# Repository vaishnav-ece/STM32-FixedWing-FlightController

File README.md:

# STM32-FixedWing-FlightController
Custom STM32-based flight controller PCB for fixed-wing UAVs featuring IMU and barometer integration, PWM servo outputs, UART/SPI/I2C/CAN interfaces, USB-C debugging, low-noise power design, PID stabilization architecture, and custom KiCad footprint development.

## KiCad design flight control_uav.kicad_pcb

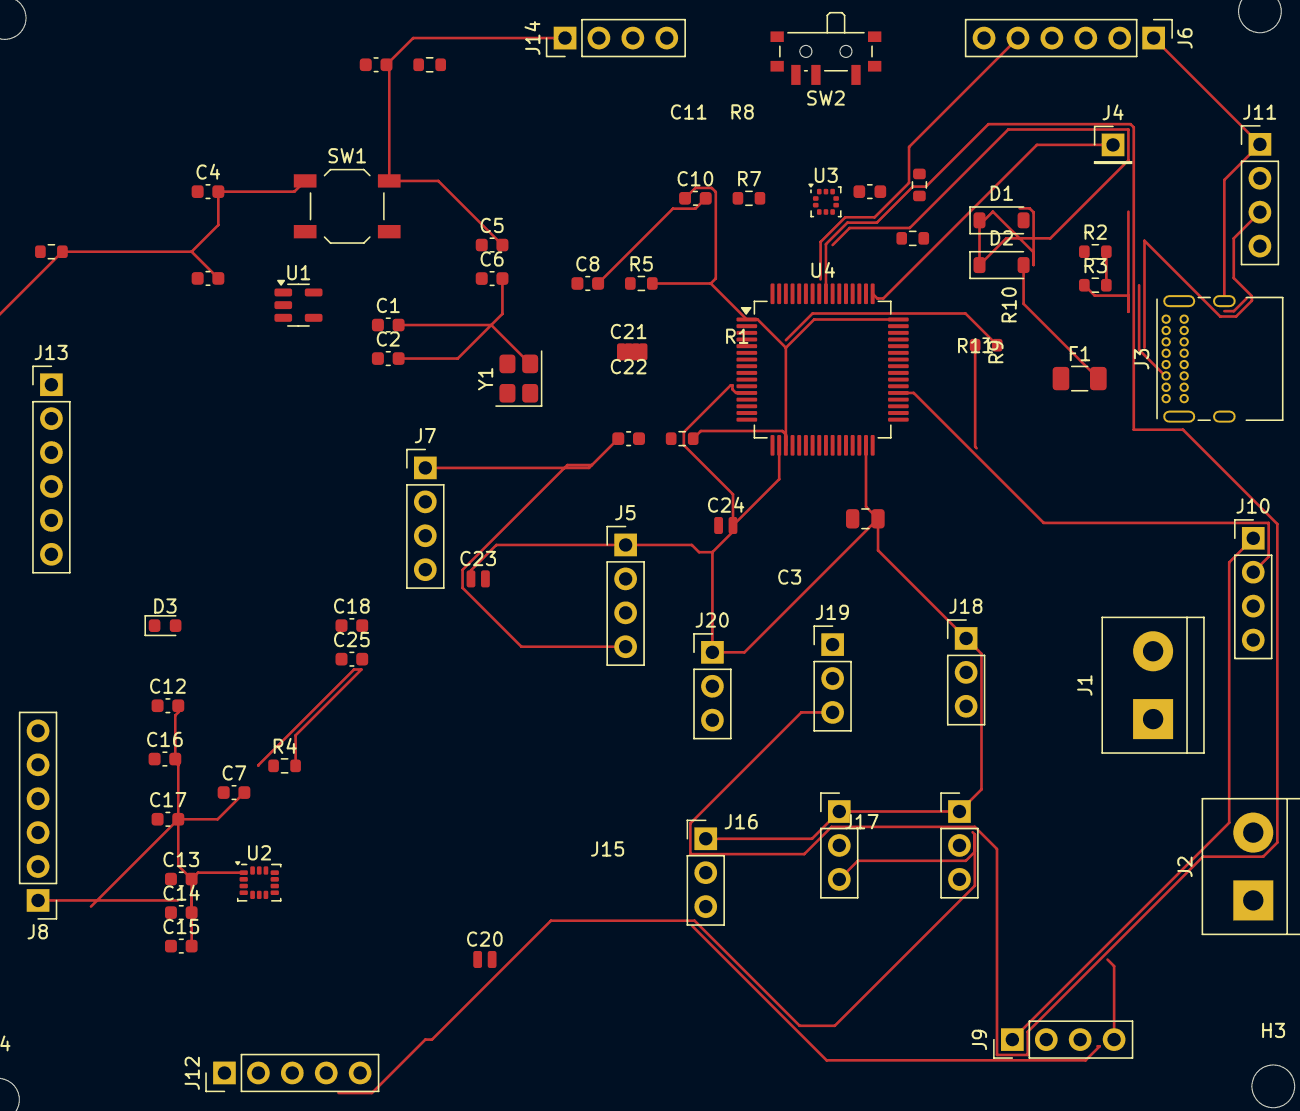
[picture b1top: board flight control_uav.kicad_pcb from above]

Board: 2 copper layers, 72 parts (0 on the bottom side), 59 nets.

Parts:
C1, C5, C6, C8, C13, C14, C15, C16, C17, C18, C25: 100n; C_0603_1608Metric
C2, C4, C7: 2u2; C_0603_1608Metric
C3, C9: 10n; C_0603_1608Metric
C10, C11: C; C_0603_1608Metric
C12: 10u; C_0603_1608Metric
C19: 4u7; C_0805_2012Metric
C20, C24: 100n; C_0504_1310Metric
C21: 1u; C_0504_1310Metric
C22, C23: 35p; C_0504_1310Metric
D1, D2: B120-E3; D_SOD-123
D3: LED; LED_0603_1608Metric
F1: Fuse; Fuse_1206_3216Metric
FB1: FerriteBead; L_0603_1608Metric
H1, H2, H3, H4: MountingHole; MountingHole_3.2mm_M3
J1: B1_IN; TerminalBlock_bornier-2_P5.08mm
J2: B2_IN; TerminalBlock_bornier-2_P5.08mm
J3: USB_IN; USB_C_Receptacle_GCT_USB4085
J4: Conn_01x02; PinHeader_1x01_P2.54mm_Vertical
J5, J7, J9, J10, J11, J14: Conn_01x04; PinHeader_1x04_P2.54mm_Vertical
J6, J8, J13: Conn_01x06; PinHeader_1x06_P2.54mm_Vertical
J12: Conn_01x05; PinHeader_1x05_P2.54mm_Vertical
J15, J16, J17, J18, J19, J20: Conn_01x03; PinHeader_1x03_P2.54mm_Vertical
R1, R2, R3, R6, R7, R9: 4K7; R_0603_1608Metric
R4, R5: 10K; R_0603_1608Metric
R8: R; R_0603_1608Metric
R10, R11: 100n; R_0603_1608Metric
SW1: SW_Push; SW_SPST_TL3342
SW2: SW_SPDT; SW_SPDT_PCM12
U1: 3V3; TSOT-23-5
U2: ICM-42670-P; LGA-14_3x2.5mm_P0.5mm_LayoutBorder3x4y
U3: BMP390; ST_HLGA-10_2x2mm_P0.5mm_LayoutBorder3x2y
U4: STM32F446RETx; LQFP-64_10x10mm_P0.5mm
Y1: Crystal_GND24; Crystal_SMD_3225-4Pin_3.2x2.5mm

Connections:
12C1_SDA: R5.1, U2.14 (AP_SDA_AP_SDIO)
12C3_SCL: R6.2, U3.2 (SCK), U4.41 (PA8)
12C3_SDA: R7.2, U3.4 (SDI), U4.40 (PC9)
+3.3V: C3.1, C4.1, C5.1, D3.2 (A), U1.5 (VOUT)
+3V3: C7.1, C8.1, C9.1, C10.1, C11.1, C12.1, C13.1, C14.1, C15.1, C16.1, C17.1, C18.1, FB1.1, J5.4, J6.6, J7.1, J8.6, J11.4, J12.1, J13.6, J14.4, R4.1, R5.2, R6.1, R7.1, R8.2, SW2.3 (C), U2.5 (VDDIO), U2.8 (VDD), U3.1 (VDDIO), U3.10 (VDD), U4.1 (VBAT), U4.19 (VDD), U4.32 (VDD), U4.48 (VDD), U4.64 (VDD)
+5: J1.2, J2.2, J15.2, J16.2, J17.2, J18.2, J20.2
/5Vusb: F1.1, J3.A4 (VBUS), J3.A9 (VBUS), J3.B4 (VBUS), J3.B9 (VBUS)
/main_root/ADC1__OUT: J11.3, R10.1
/main_root/ADC2__OUT: J11.2, R11.1
/main_root/ADC__IN0: C24.1, R10.2, U4.14 (PA0)
/main_root/ADC__IN1: C25.1, R11.2, U4.15 (PA1)
/main_root/CAN2_RX: J5.3, U4.33 (PB12)
/main_root/CAN2_TX: J5.2, U4.34 (PB13)
/main_root/DSC_OUT: C22.2, U4.6 (PH1), Y1.3
/main_root/GPIOIN_0: J14.3, U4.61 (PB8)
/main_root/GPIOIN_1: J14.2, U4.62 (PB9)
/main_root/GPIOOUT_0: J13.5, U4.11 (PC3)
/main_root/GPIOOUT_1: J13.4, U4.10 (PC2)
/main_root/GPIOOUT_2: J13.3, U4.9 (PC1)
/main_root/GPIOOUT_3: J13.2, U4.8 (PC0)
/main_root/GPIOOUT_4: J12.2, U4.2 (PC13)
/main_root/GPIOOUT_5: J12.3, U4.3 (PC14)
/main_root/GPIOOUT_6: J12.4, U4.4 (PC15)
/main_root/SPI1__5CK: J8.4, U4.21 (PA5)
/main_root/SPI1__MISO: J8.3, U4.22 (PA6)
/main_root/SPI1__MOS1: J8.2, U4.23 (PA7)
/main_root/SPI1__NSS: J8.5, U4.20 (PA4)
/main_root/SPI3__5CK: J6.4, U4.51 (PC10)
/main_root/SPI3__MISO: J6.3, U4.52 (PC11)
/main_root/SPI3__MOSI: J6.2, U4.53 (PC12)
/main_root/SPI3__NSS: J6.5, U4.50 (PA15)
/main_root/SWDIO: J4.1, U4.49 (PA14)
/main_root/TIM2_CH2: J15.3, U4.55 (PB3)
/main_root/TIM2_CH3: J16.3, U4.29 (PB10)
/main_root/TIM3_CH1: J18.3, U4.57 (PB5)
/main_root/TIM3_CH2: J19.3, U4.56 (PB4)
/main_root/TIM3_CH4: J20.3, U4.27 (PB1)
/main_root/USART1__TX: J7.2, U4.43 (PA10)
/main_root/USART2_RX: J9.3, U4.17 (PA3)
/main_root/USART2_TX: J9.2, U4.16 (PA2)
/main_root/USART6_RX: J10.3, U4.38 (PC7)
/main_root/USART6_TX: J10.2, U4.37 (PC6)
/main_root/USART__RX: J7.3, U4.42 (PA9)
GND: C1.2, C2.2, C3.2, C4.2, C5.2, C6.2, C7.2, C8.2, C9.2, C10.2, C11.2, C12.2, C13.2, C14.2, C15.2, C16.2, C17.2, C18.2, C19.2, C20.2, C21.2, C22.1, C23.1, C24.2, C25.2, J3.A1 (GND), J3.A12 (GND), J3.B1 (GND), J3.B12 (GND), J3.S1 (SHIELD), J5.1, J6.1, J7.4, J8.1, J9.4, J10.4, J11.1, J12.5, J13.1, J14.1, J15.1, J16.1, J17.1, J18.1, J20.1, R1.2, R8.1, SW1.1, SW2.1 (A), U1.2 (GND), U2.1 (AP_SDO_AP_AD0), U2.6 (GND), U3.3 (VSS), U3.5 (SDO), U3.7 (CSB), U3.9 (VSS), U4.12 (VSSA), U4.18 (VSS), U4.31 (VSS), U4.47 (VSS), U4.63 (VSS), Y1.2, Y1.4
NRST: C6.1, SW1.2, U4.7 (NRST)
unnamed: C23.2, Y1.1
unnamed: C1.1, C2.1, D1.1 (K), D2.1 (K), U1.1 (VIN), U1.3 (EN)
unnamed: D2.2 (A), F1.2
unnamed: D3.1 (K), R1.1
unnamed: J3.A5 (CC1), R3.1
unnamed: J3.B5 (CC2), R2.1
unnamed: J9.1, J10.1
unnamed: R2.2, R3.2
unnamed: R9.1, SW2.2 (B)
unnamed: R9.2, U4.60 (BOOT0)
unnamed: C19.1, U4.30 (VCAP_1)
unnamed: C20.1, C21.1, FB1.2, U4.13 (VDDA)
USB-D+: J3.A6 (D+), J3.B6 (D+), U4.45 (PA12)
USB-D-: J3.A7 (D-), J3.B7 (D-), U4.44 (PA11)

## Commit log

2026-05-14 Initial commit - STM32 flight controller PCB design
